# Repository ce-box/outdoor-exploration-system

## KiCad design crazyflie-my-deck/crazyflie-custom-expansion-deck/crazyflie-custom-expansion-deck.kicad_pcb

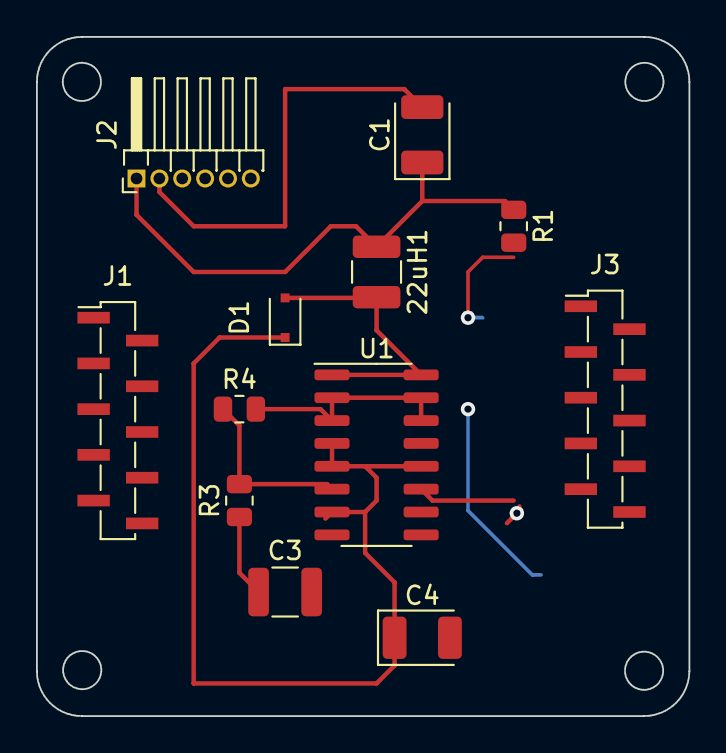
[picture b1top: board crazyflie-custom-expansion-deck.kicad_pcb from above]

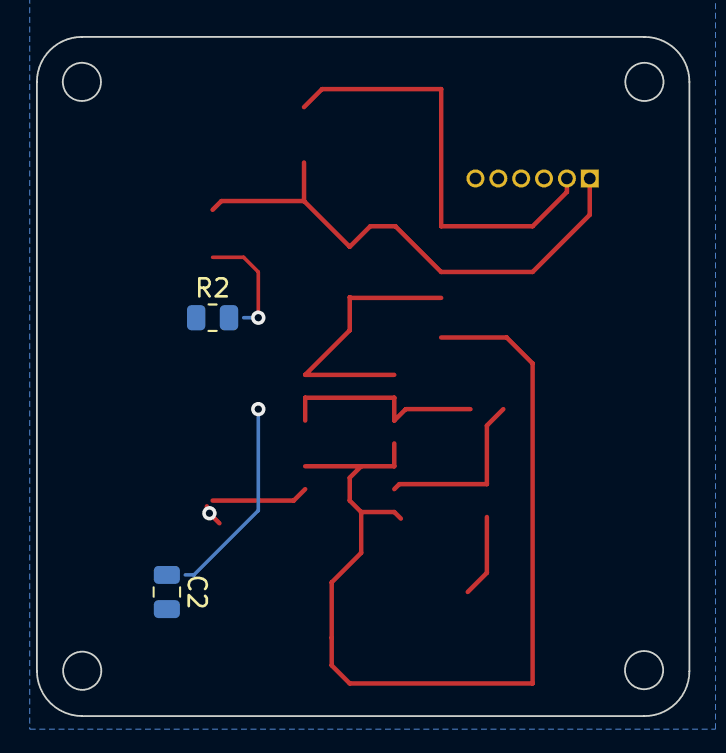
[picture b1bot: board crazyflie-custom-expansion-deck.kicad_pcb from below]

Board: 2 copper layers, 36.2 x 37.7 mm, 14 parts (2 on the bottom side), 8 nets.

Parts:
22uH1: L; L_1210_3225Metric
C1, C4: 100uF; CP_EIA-3528-15_AVX-H
C2: 0.1uF; C_0805_2012Metric
C3: 10uF; C_1210_3225Metric
D1: 1SS355VM; D_SOD-323F
J1, J3: Conn_01x10; PinSocket_1x10_P1.27mm_Vertical_SMD_Pin1Left
J2: Conn_01x06_Male; PinHeader_1x06_P1.27mm_Horizontal
R1: 120k; R_0805_2012Metric
R2: 30k; R_0805_2012Metric
R3: 390k; R_0805_2012Metric
R4: 130k; R_0805_2012Metric
U1: MAX7111; SOIC-16_3.9x9.9mm_P1.27mm

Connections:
GND: C1.2, C2.2, C3.2, C4.2, J2.2, R2.2, R4.2, U1.2 (PGD), U1.3 (ILM), U1.14 (GN), U1.15 (PGD)
unnamed: 22uH1.1, C1.1, J2.1, R1.1
unnamed: 22uH1.2, D1.2 (A), U1.1 (LX), U1.16 (LX)
unnamed: C2.1, U1.10 (LB-), U1.13 (RF)
unnamed: C3.1, R3.1, U1.9 (OP)
unnamed: C4.1, D1.1 (K), U1.4 (SDN), U1.5 (SBY), U1.7 (NE), U1.12 (PS)
unnamed: R1.2, R2.1, U1.11 (LB+)
unnamed: R3.2, R4.1, U1.6 (FB)

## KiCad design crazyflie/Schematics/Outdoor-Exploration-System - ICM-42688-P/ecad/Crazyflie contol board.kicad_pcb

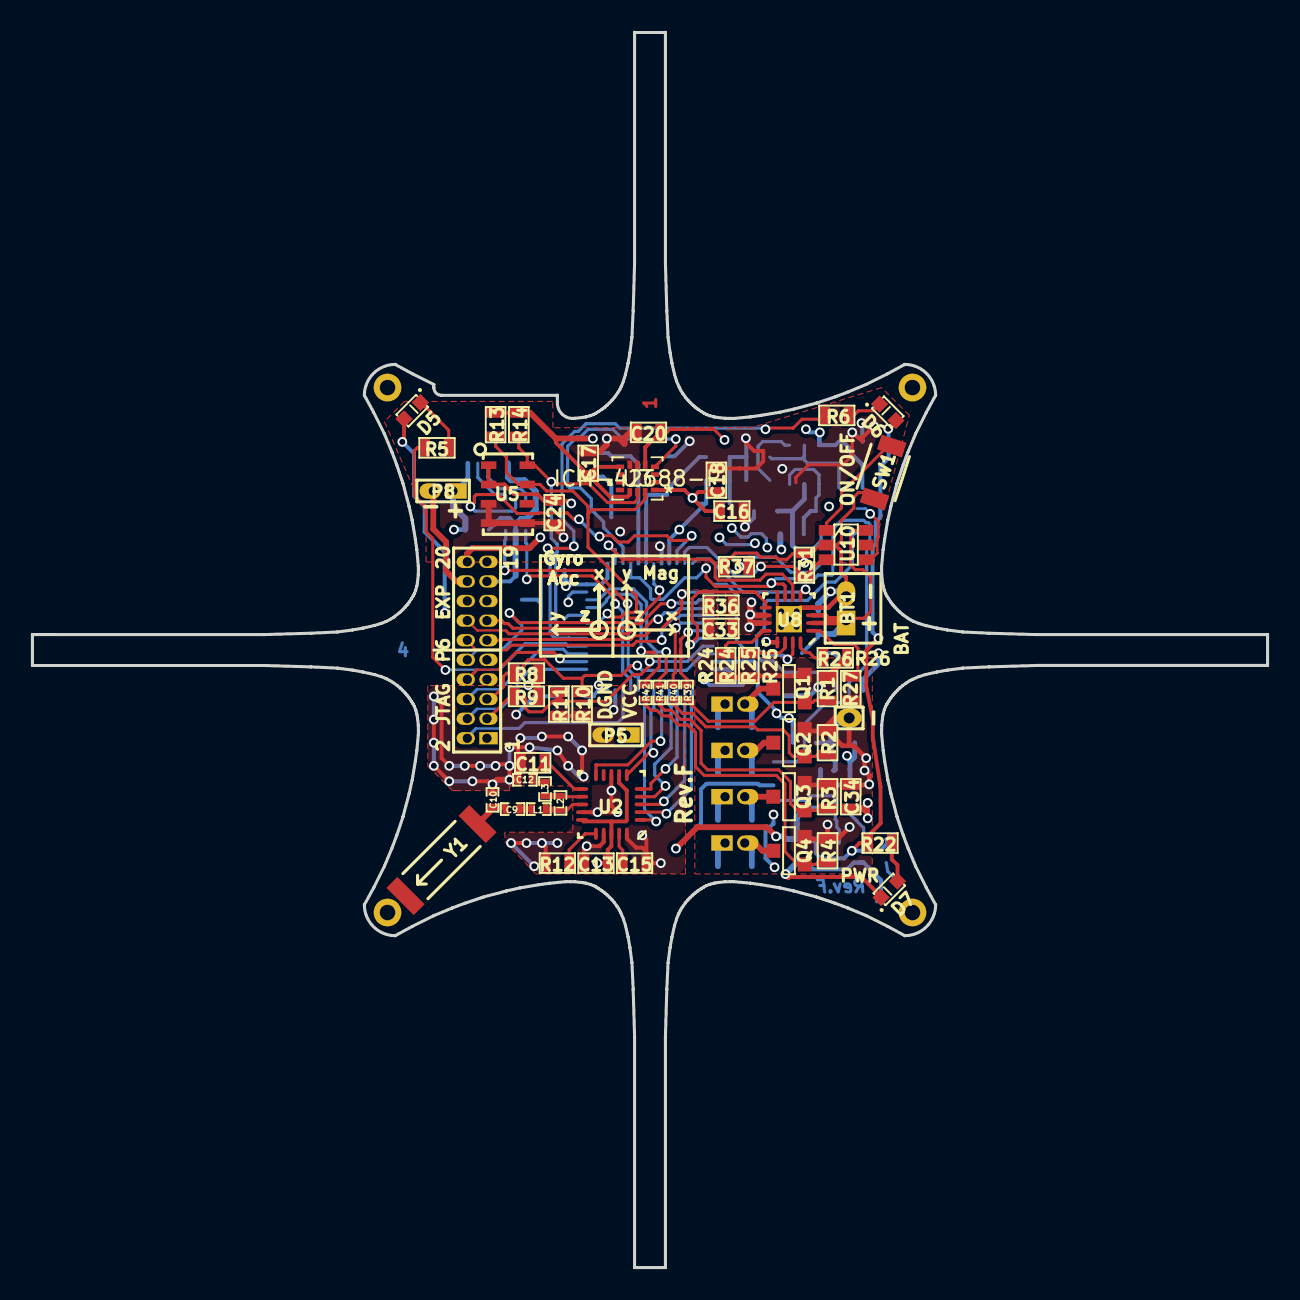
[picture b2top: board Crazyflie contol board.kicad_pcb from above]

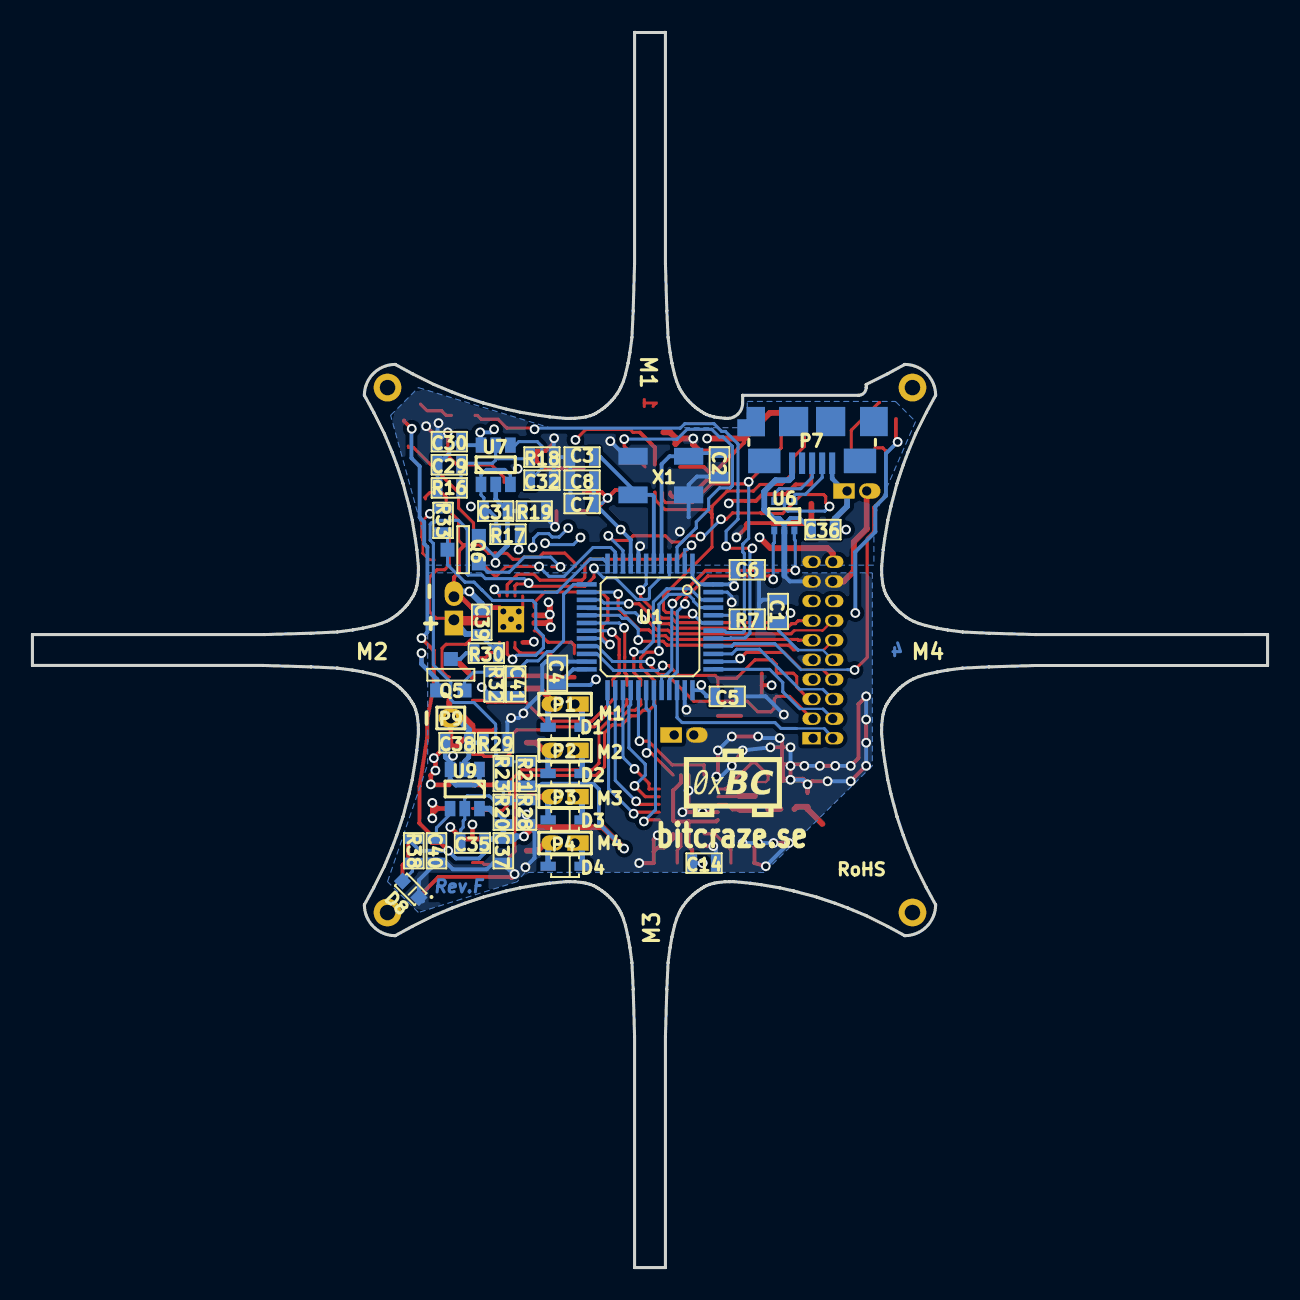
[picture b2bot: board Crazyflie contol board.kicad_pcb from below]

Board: 4 copper layers, 80.0 x 80.0 mm, 115 parts (52 on the bottom side), 81 nets.

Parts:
BT1: BATTERY; JST-B2B-ZR
C1, C4, C5, C14, C18, C20, C24, C33, C36, C38, C41: 100nF; SM0603_Capa
C2, C3, C29, C35: 15pF; SM0603_Capa
C6, C7, C30, C31, C34, C37: 4.7uF; SM0603_Capa
C8, C13, C16, C32, C40: 10nF; SM0603_Capa
C9: 1.5pF; SM0402
C10: 1.0pF; SM0402
C11: 2.2nF; SM0603
C12: 4.7pF; SM0402
C15: 33nF; SM0603_Capa
C17: 2.2nF; SM0603_Capa
C39: 10uF; SM0603_Capa
D1, D2, D3, D4: BAT54; sod323
D5: RED LED; SMDLED-0603
D6: GREEN LED; SMDLED-0603
D7, D8: BLUE LED; SMDLED-0603
L1: 3.9nH; SM0402
L2: 8.2nH; SM0402
L3: 2.7nH; SM0402
P1, P2, P3, P4, P5, P8: CONN_2; PINHEADER_127_2X1
P6: CONN_10X2; PINHEADER_127_2X10
P7: MICRO-B-USB; ZX62-B-5PA_11_CFK
P9: CONN_1; PINHEADER_127_1X1
PCB_EDGE1: VAL**; EDGE_S_LONG_USB
PCB_EDGE2, PCB_EDGE2#2, PCB_EDGE2#3: VAL**; EDGE_S_LONG
Q1, Q2, Q3, Q4: PMV31XN; SOT23GDS
Q5, Q6: 2N7002; SOT23GDS
R1, R2, R3, R4, R8, R9, R25, R27, R32, R33, R36, R37: 10k; SM0603
R5: 330R; SM0603
R6: 220R; SM0603
R7, R31: 100k; SM0603
R10, R11: NM; SM0603
R12: 22k; SM0603
R13, R14: 2.2k; SM0603
R16: 39k; SM0603
R17: 10R; SM0603
R18, R28: 30k; SM0603
R19, R29: 0R; SM0603
R20: 42.2k; SM0603
R21: 300k; SM0603
R22, R38: 1k; SM0603
R23: 150k; SM0603
R24: 1.2k; SM0603
R26: 1.2K; SM0603
R30: 20k; SM0603
R39, R40, R41, R42: 100R; SM0402
SW1: PUSH ON/OFF; SPST-NO-4x2.5
U1: STM32F103CB; LQFP-48
U2: NRF24L01+; QFN20-4x4mm
U3: ICM-42688-P
U5: MS5611-01BA03; MS5611
U6: NUF2221; SOT363
U7, U9: TPS79301; SOT23_6
U8: BQ24075; QFN16
U10: MAX16054; SOT23_6
X1: 16Mhz; XTAL-5.0x3.2
Y1: CHIP_ANTENNA; CHIP-ANT-6.5x2.2

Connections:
+BATT: BT1.1, C39.1, D1.2, D2.2, D3.2, D4.2, P1.1, P2.1, P3.1, P4.1, R30.2, U8.2, U8.3, U10.6
/BOOT0: R7.1, U1.44
/CHG: U1.20, U8.9
/EN1: U1.2, U8.6
/EN2: U1.12, U8.5
/EXT_I2C_SCL/TX: P6.3, R9.2, R11.1, U1.21
/EXT_I2C_SDA/RX: P6.5, R8.2, R10.1, U1.22
/EXT_SPI_CS: P6.11, U1.14
/EXT_SPI_MISO: P6.14, U1.16
/EXT_SPI_MOSI: P6.12, U1.17
/EXT_SPI_SCK: P6.13, U1.15
/I2C_SCK_VCCA: R13.2, U1.43, U3.14, U5.7
/I2C_SCL_VCCA: R14.2, U1.42, U3.13, U5.8
/INT_GA: U1.3, U3.4
/LED_GREEN: R6.1, U1.41
/LED_RED: R5.1, U1.40
/MOTOR1: R39.1, U1.19
/MOTOR2: R40.1, U1.18
/MOTOR3: R41.1, U1.46
/MOTOR4: R42.1, U1.45
/PGOOD: R21.1, R23.2, U1.4, U8.7
/POWER/D+: P7.3, U6.6
/POWER/D-: P7.2, U6.4
/POWER/USBD+: U1.33, U6.1
/POWER/USBD-: U1.32, U6.3
/POWER/USB_CON: U1.10, U6.5
/POWER/VBAT: C41.1, Q5.S, R32.2, U1.13
/POWER/VUSB: C36.1, P7.1, P8.1, Q6.G, R37.2, U8.13
/SNRST: C1.1, P6.10, U1.7
/SPI_MISO: U1.27, U2.5
/SPI_MOSI: U1.28, U2.4
/SPI_SCK: U1.26, U2.3
/SYSOFF: R31.2, U1.11, U10.3
/TCK: P6.4, U1.37
/TDI: P6.8, U1.38
/TDO: P6.6, U1.39
/TMS: P6.2, U1.34
/WIRELESS/W_CS: U1.25, U2.2
/W_CE: U1.31, U2.1
/W_CK: U1.29, U2.10
/W_INT: U1.30, U2.6
AGND: C2.2, C3.2, C7.2, C8.2, C16.2, C17.2, C18.2, C20.2, C24.2, C30.2, C32.2, P6.19, R18.1, R19.1, U1.8, U3.6, U3.7, U5.3, U5.4, U5.5, X1.2, X1.4
DGND: C1.2, C4.2, C5.2, C6.2, C10.2, C11.2, C12.2, C13.2, C14.2, C15.2, C36.2, C37.2, C40.2, D7.2, D8.2, P5.2, P6.9, P6.17, P6.18, P7.5, P8.2, R7.2, R10.2, R11.2, R12.2, R28.1, R29.1, U1.23, U1.35, U1.47, U2.8, U2.14, U2.17, U2.20, U6.2
GND: BT1.2, C31.2, C33.2, C34.2, C38.2, C39.2, C41.2, P9.1, Q1.S, Q2.S, Q3.S, Q4.S, Q6.S, R1.2, R2.2, R3.2, R4.2, R19.2, R24.1, R25.1, R26.1, R27.1, R29.2, R31.1, R32.1, R36.1, R37.1, SW1.1, U7.2, U8.4, U8.8, U8.17, U9.2, U10.2
unnamed: C9.2, L1.1
unnamed: C9.1, C10.1
unnamed: C11.1, C12.1, L3.1
unnamed: L2.2, L3.2
unnamed: L1.2, L2.1
unnamed: C2.1, U1.5, X1.1
unnamed: C3.1, U1.6, X1.3
unnamed: C15.1, U2.19
unnamed: C29.2, R16.1, R18.2, U7.5
unnamed: C31.1, R17.1, U7.1, U7.3
unnamed: C32.1, U7.4
unnamed: C35.2, R20.1, R23.1, R28.2, U9.5
unnamed: C40.1, U9.4
unnamed: P1.2, Q1.D
unnamed: P2.2, Q2.D
unnamed: P3.2, Q3.D
unnamed: P4.2, Q4.D
unnamed: D5.2, R5.2
unnamed: D6.2, R6.2
unnamed: D7.1, R22.1
unnamed: D8.1, R38.1
unnamed: Q1.G, R39.2
unnamed: Q2.G, R40.2
unnamed: Q3.G, R41.2
unnamed: Q4.G, R42.2
unnamed: Q5.D, R30.1
unnamed: Q6.D, R33.2, U8.15
unnamed: R12.1, U2.16
unnamed: R24.2, U8.12
unnamed: R25.2, U8.14
unnamed: R26.2, U8.16
unnamed: R27.2, U8.1
unnamed: R33.1, U10.4
unnamed: SW1.2, U10.1
VCC: C4.1, C5.1, C6.1, C13.1, C14.1, C35.1, C37.1, D5.1, D6.1, P5.1, P6.1, P6.15, R8.1, R9.1, R20.2, R21.2, R22.2, R38.2, U1.1, U1.24, U1.36, U1.48, U2.7, U2.15, U2.18, U9.6
VCCA: C7.1, C8.1, C16.1, C17.1, C18.1, C20.1, C24.1, C29.1, C30.1, P6.20, R13.1, R14.1, R16.2, U1.9, U3.1, U3.5, U3.8, U3.12, U5.1, U5.2, U7.6
VCOM: C33.1, C34.1, C38.1, P6.16, Q5.G, R17.2, R36.2, U8.10, U8.11, U9.1, U9.3

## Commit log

2022-03-26 [add] backup
2022-08-17 Crazyflie expansion deck template added
2022-09-21 cpu-backup
2022-10-18 [add] boost voltage
2022-10-31 acomodo de componentes
2022-11-01 Modulo ESP32 CAM
2022-11-01 Libería y Modelos de ESP32 CAM
2022-11-03 Schematics for Voltage Booster
    Connections and change of pins for MAX711
2022-11-04 Fixes
2022-11-04 Tracks - voltage boost
    Falta 1 y las tracks a GND

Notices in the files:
parts and their libraries:
Copyright 2021 Accelerated Designs. All rights reserved.
